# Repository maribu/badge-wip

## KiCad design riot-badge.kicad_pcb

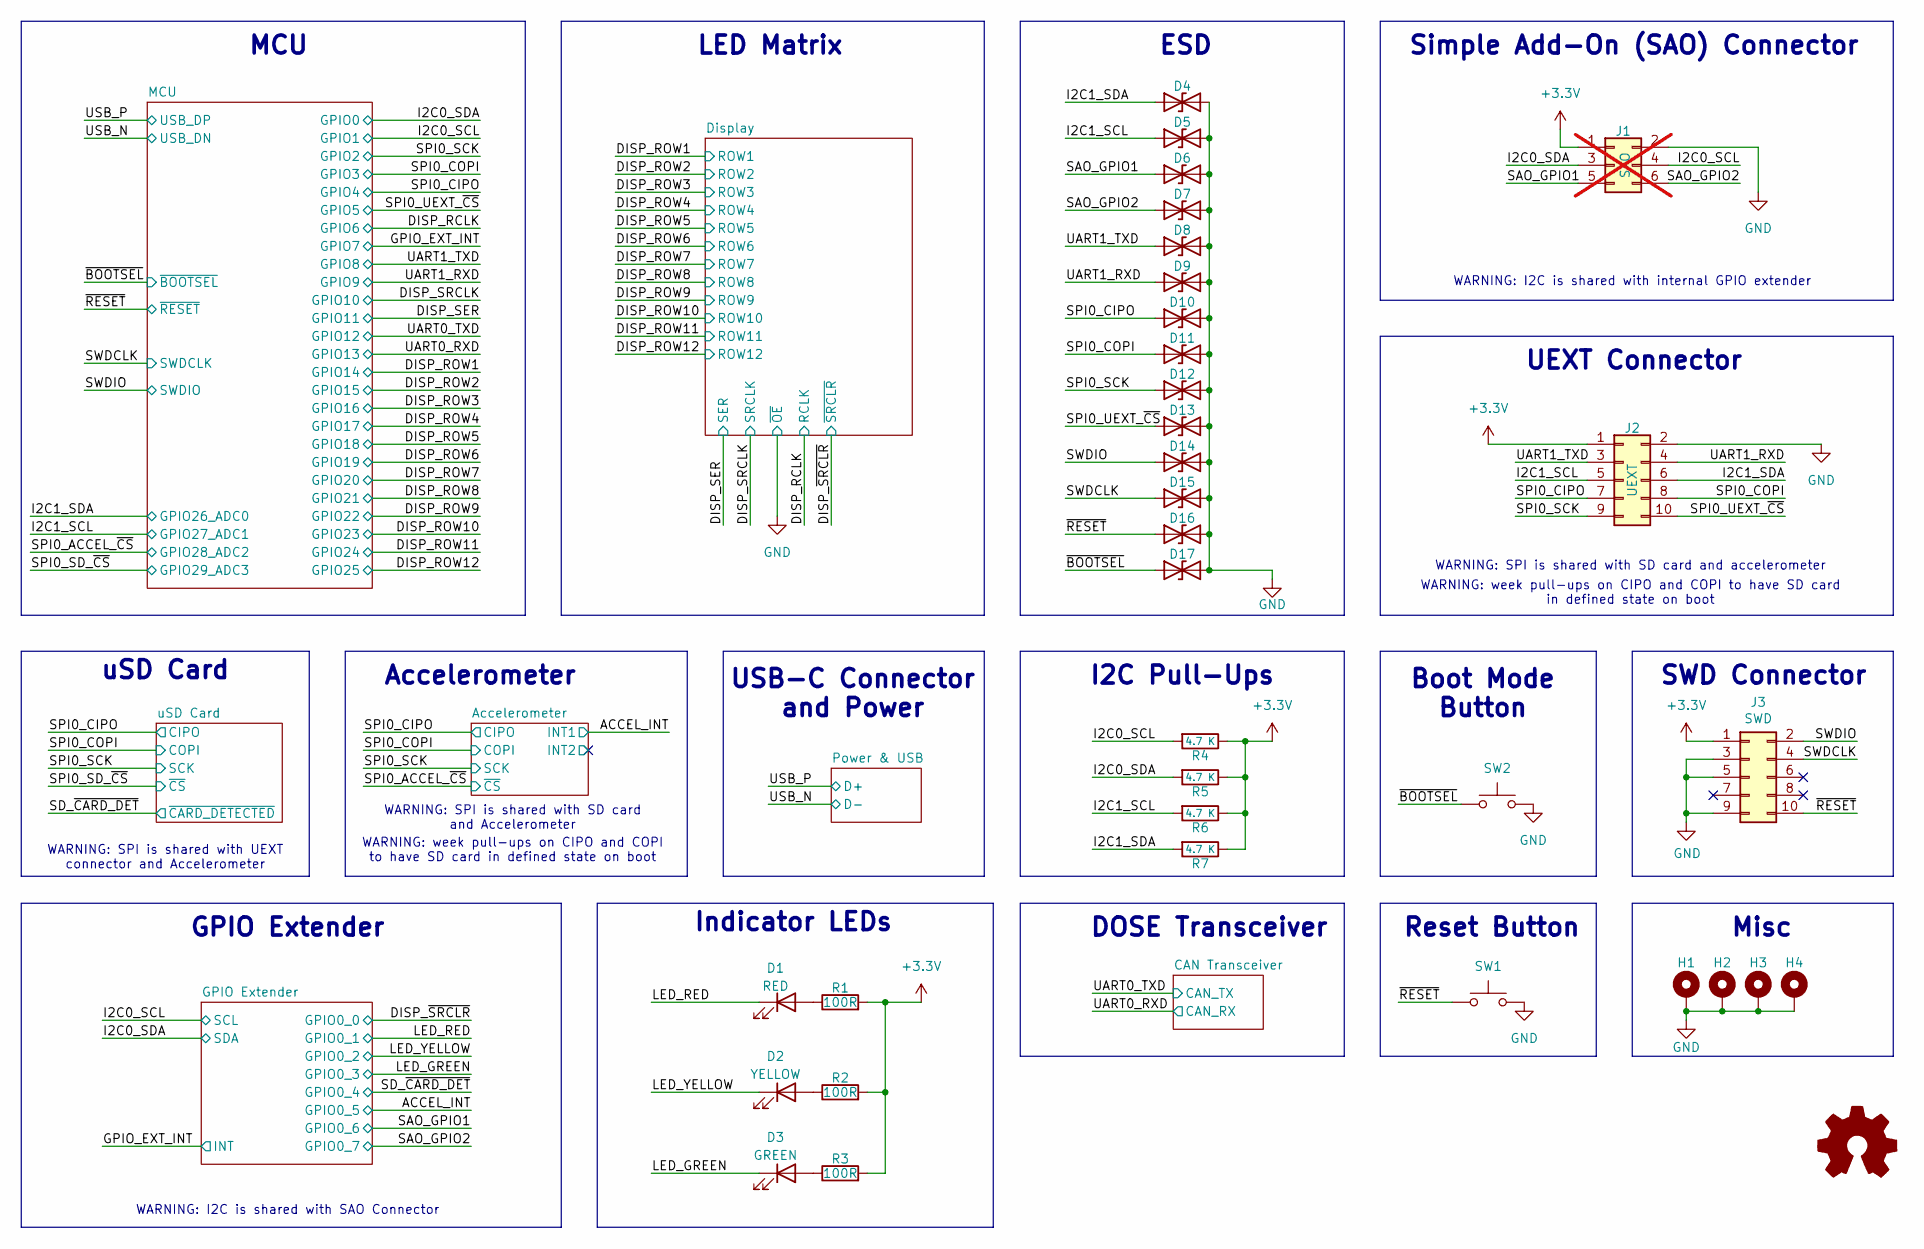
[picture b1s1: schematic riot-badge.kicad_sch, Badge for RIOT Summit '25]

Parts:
D1: RED; LED_0603_1608Metric; LCSC C2286
D2: YELLOW; LED_0805_2012Metric; LCSC C2296
D3: GREEN; LED_0805_2012Metric; LCSC C2297
D4, D5, D6, D7, D8, D9, D10, D11, D12, D13, D14, D15, D16, D17: D_TVS; SOD-882_L1.0-W0.6-BI; LCSC C7420372
G1: Logo_Open_Hardware_Small; OSHW-Logo2_7.3x6mm_SilkScreen
H1, H2, H3, H4: MountingHole_Pad; MountingHole_2.2mm_M2_DIN965_Pad
J1: SAO; PinSocket_2x03_P2.54mm_Vertical_SAO; LCSC C18164972; not fitted
J2: UEXT; HDR-TH_10P-P2.54-V-F-R2-C5-S2.54_GREENCONN; LCSC C7434489
J3: SWD; CONN-SMD_FTSH-105-01-L-DV-K-TR; LCSC C448647
R1, R2, R3: 100R; R_0402_1005Metric; LCSC C25076
R4, R5, R6, R7: 4.7 K; R_0402_1005Metric; LCSC C25900
SW1, SW2: SW_Push; SW-SMD_4P-L5.1-W5.1-P3.70-LS6.5-TL_H1.5; LCSC C318884

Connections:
+3.3V: J1.1, J2.1, J3.1, R1.2, R2.2, R3.2, R4.1, R5.1, R6.1, R7.1; also elsewhere on the board
/I2C0_SCL: J1.4, R4.2; also elsewhere on the board
/I2C0_SDA: J1.3, R5.2; also elsewhere on the board
/I2C1_SCL: D5.1 (A1), J2.5, R6.2; also elsewhere on the board
/I2C1_SDA: D4.1 (A1), J2.6, R7.2; also elsewhere on the board
/LED_GREEN: D3.1 (K); also elsewhere on the board
/LED_RED: D1.1 (K); also elsewhere on the board
/LED_YELLOW: D2.1 (K); also elsewhere on the board
/SAO_GPIO1: D6.1 (A1), J1.5; also elsewhere on the board
/SAO_GPIO2: D7.1 (A1), J1.6; also elsewhere on the board
/SPI0_CIPO: D10.1 (A1), J2.7; also elsewhere on the board
/SPI0_COPI: D11.1 (A1), J2.8; also elsewhere on the board
/SPI0_SCK: D12.1 (A1), J2.9; also elsewhere on the board
/SPI0_UEXT_~CS: D13.1 (A1), J2.10; also elsewhere on the board
/SWDCLK: D15.1 (A1), J3.4; also elsewhere on the board
/SWDIO: D14.1 (A1), J3.2; also elsewhere on the board
/UART1_RXD: D9.1 (A1), J2.4; also elsewhere on the board
/UART1_TXD: D8.1 (A1), J2.3; also elsewhere on the board
/~BOOTSEL: D17.1 (A1), SW2.1; also elsewhere on the board
/~RESET: D16.1 (A1), J3.10, SW1.1; also elsewhere on the board
GND: D4.2 (A2), D5.2 (A2), D6.2 (A2), D7.2 (A2), D8.2 (A2), D9.2 (A2), D10.2 (A2), D11.2 (A2), D12.2 (A2), D13.2 (A2), D14.2 (A2), D15.2 (A2), D16.2 (A2), D17.2 (A2), H1.1, H2.1, H3.1, H4.1, J1.2, J2.2, J3.3, J3.5, J3.9, SW1.2, SW2.2; also elsewhere on the board
unnamed: D1.2 (A), R1.1
unnamed: D2.2 (A), R2.1
unnamed: D3.2 (A), R3.1

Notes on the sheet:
UEXT Connector
Misc
uSD Card
GPIO Extender
Boot Mode Button
Indicator LEDs
WARNING: week pull-ups on CIPO and COPI to have SD card in defined state on boot
Reset Button
LED Matrix
WARNING: SPI is shared with UEXT connector and Accelerometer
DOSE Transceiver
ESD
WARNING: SPI is shared with SD card and accelerometer
I2C Pull-Ups
WARNING: I2C is shared with internal GPIO extender
WARNING: I2C is shared with SAO Connector
Simple Add-On (SAO) Connector
SWD Connector
WARNING: week pull-ups on CIPO and COPI to have SD card in defined state on boot
USB-C Connector and Power
WARNING: SPI is shared with SD card and Accelerometer
MCU
Accelerometer

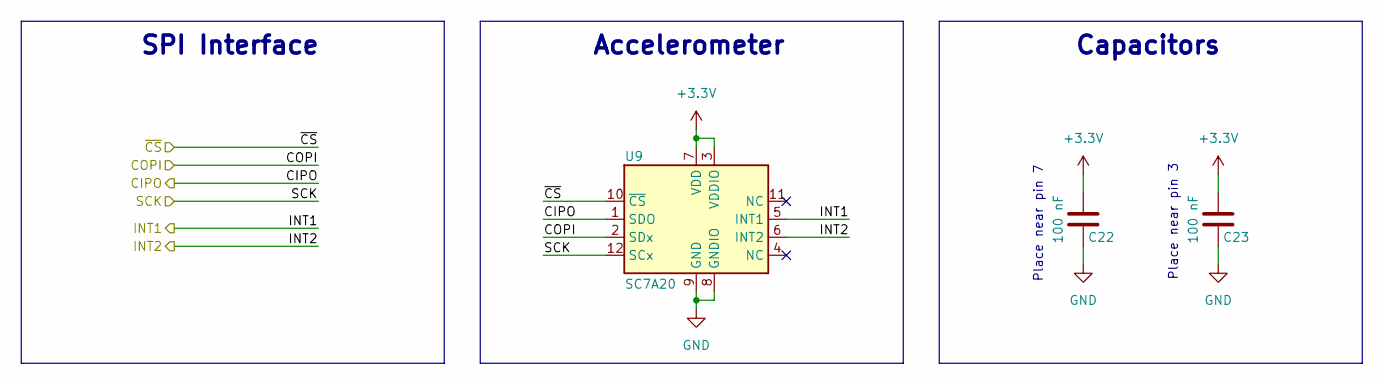
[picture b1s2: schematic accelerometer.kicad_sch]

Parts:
C22, C23: 100 nF; C_0402_1005Metric; LCSC C1525
U9: SC7A20; LGA-12_2x2mm_P0.5mm

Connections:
+3.3V: C22.1, C23.1, U9.3 (VDDIO), U9.7 (VDD); also elsewhere on the board
/ACCEL_INT: U9.5 (INT1); also elsewhere on the board
/Accelerometer/INT2: U9.6 (INT2)
/SPI0_ACCEL_~CS: U9.10 (~CS); also elsewhere on the board
/SPI0_CIPO: U9.1 (SDO); also elsewhere on the board
/SPI0_COPI: U9.2 (SDx); also elsewhere on the board
/SPI0_SCK: U9.12 (SCx); also elsewhere on the board
GND: C22.2, C23.2, U9.8 (GNDIO), U9.9 (GND); also elsewhere on the board

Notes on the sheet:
SPI Interface
Capacitors
Place near pin 7
Place near pin 3
Accelerometer

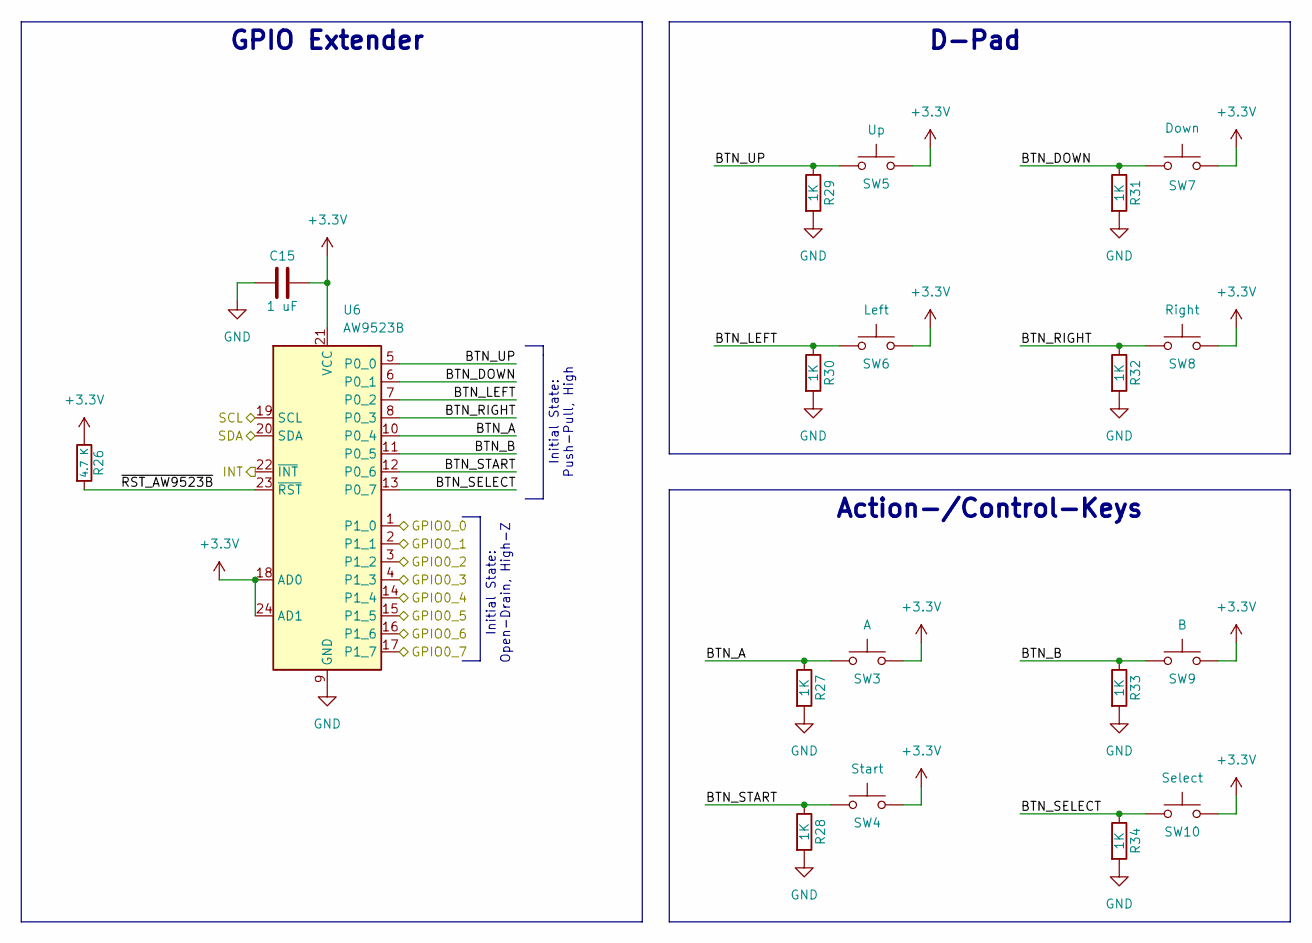
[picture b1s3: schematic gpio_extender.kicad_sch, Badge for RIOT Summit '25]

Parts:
C15: 1 uF; C_0402_1005Metric; LCSC C52923
R26: 4.7 K; R_0402_1005Metric; LCSC C25900
R27, R28, R29, R30, R31, R32, R33, R34: 1K; R_0402_1005Metric; LCSC C11702
SW3, SW4, SW5, SW6, SW7, SW8, SW9, SW10: SW_Push; SW-SMD_4P-L5.1-W5.1-P3.70-LS6.5-TL_H1.5; LCSC C318884
U6: AW9523B; QFN-24-1EP_4x4mm_P0.5mm_EP2.7x2.7mm

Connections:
+3.3V: C15.2, R26.1, SW3.2, SW4.2, SW5.2, SW6.2, SW7.2, SW8.2, SW9.2, SW10.2, U6.18 (AD0), U6.21 (VCC), U6.24 (AD1); also elsewhere on the board
/ACCEL_INT: U6.15 (P1_5); also elsewhere on the board
/DISP_~SRCLR: U6.1 (P1_0); also elsewhere on the board
/GPIO Extender/BTN_A: R27.1, SW3.1, U6.10 (P0_4)
/GPIO Extender/BTN_B: R33.1, SW9.1, U6.11 (P0_5)
/GPIO Extender/BTN_DOWN: R31.1, SW7.1, U6.6 (P0_1)
/GPIO Extender/BTN_LEFT: R30.1, SW6.1, U6.7 (P0_2)
/GPIO Extender/BTN_RIGHT: R32.1, SW8.1, U6.8 (P0_3)
/GPIO Extender/BTN_SELECT: R34.1, SW10.1, U6.13 (P0_7)
/GPIO Extender/BTN_START: R28.1, SW4.1, U6.12 (P0_6)
/GPIO Extender/BTN_UP: R29.1, SW5.1, U6.5 (P0_0)
/GPIO Extender/~RST_AW9523B: R26.2, U6.23 (~RST)
/GPIO_EXT_INT: U6.22 (~INT); also elsewhere on the board
/I2C0_SCL: U6.19 (SCL); also elsewhere on the board
/I2C0_SDA: U6.20 (SDA); also elsewhere on the board
/LED_GREEN: U6.4 (P1_3); also elsewhere on the board
/LED_RED: U6.2 (P1_1); also elsewhere on the board
/LED_YELLOW: U6.3 (P1_2); also elsewhere on the board
/SAO_GPIO1: U6.16 (P1_6); also elsewhere on the board
/SAO_GPIO2: U6.17 (P1_7); also elsewhere on the board
/SD_~CARD_DET: U6.14 (P1_4); also elsewhere on the board
GND: C15.1, R27.2, R28.2, R29.2, R30.2, R31.2, R32.2, R33.2, R34.2, U6.9 (GND), U6.25 (GND); also elsewhere on the board

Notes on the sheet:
Initial State: Push-Pull, High
D-Pad
Action-/Control-Keys
GPIO Extender
Initial State: Open-Drain, High-Z

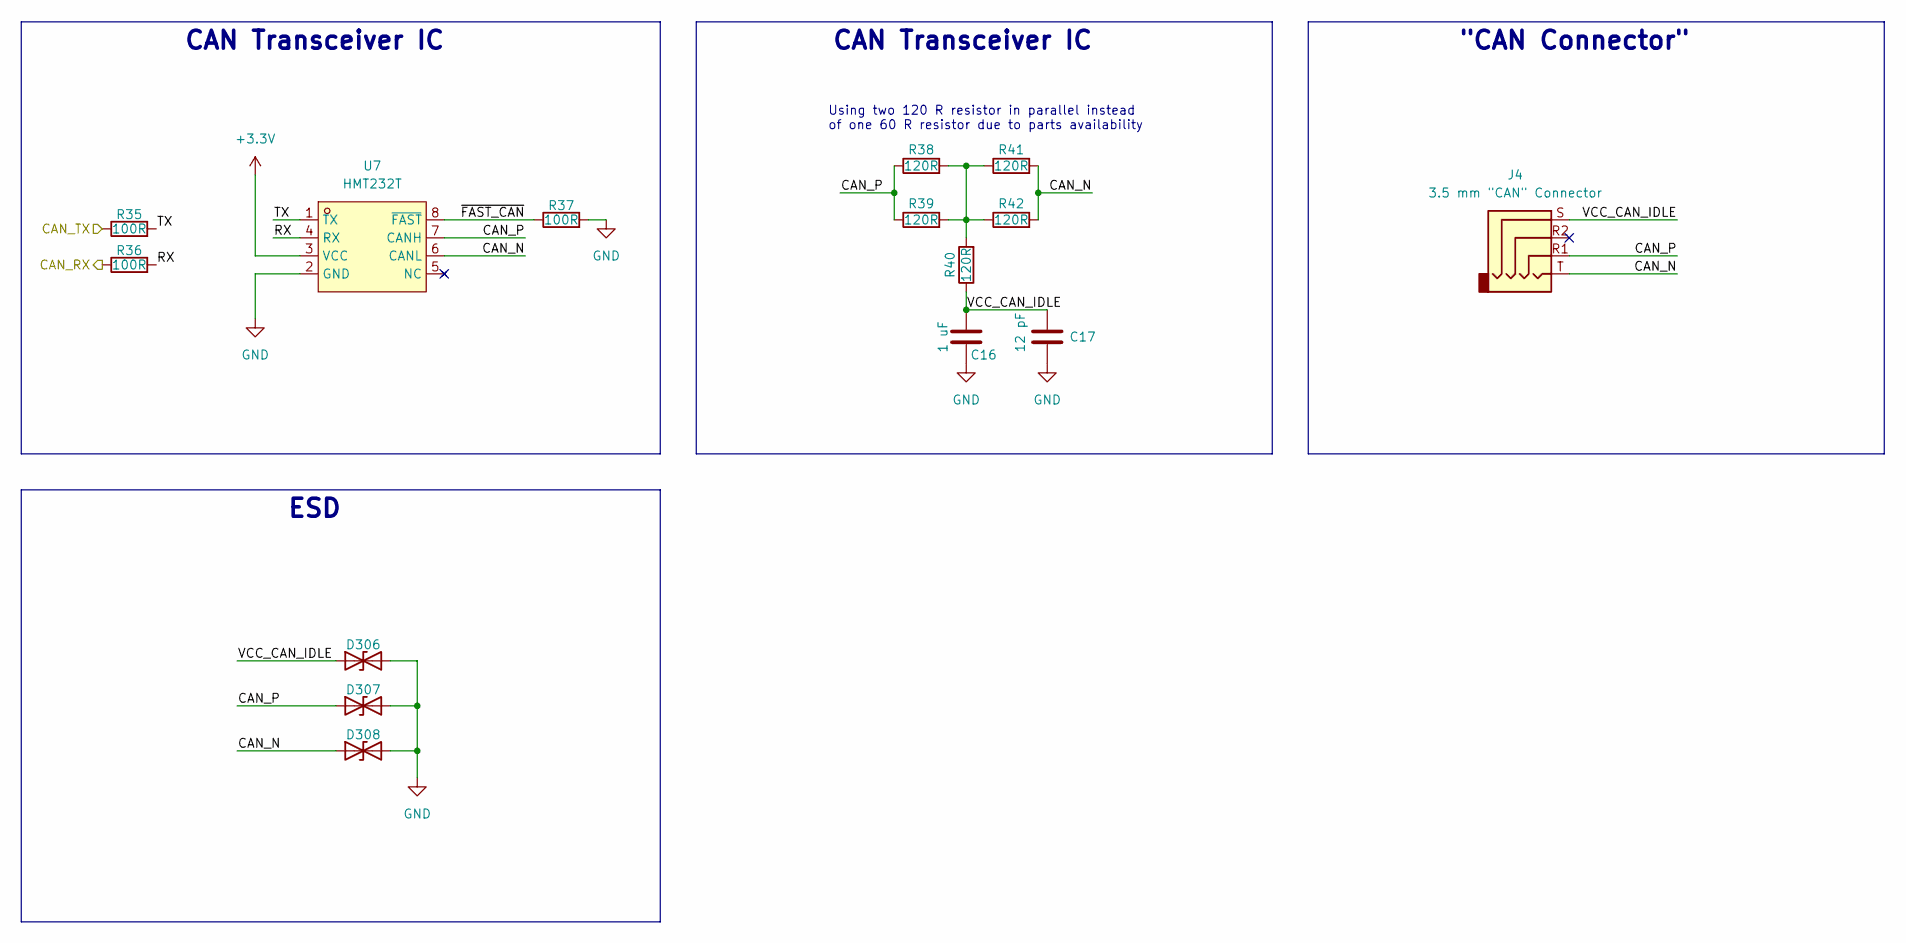
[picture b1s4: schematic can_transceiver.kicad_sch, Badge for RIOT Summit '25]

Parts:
C16: 1 uF; C_0402_1005Metric; LCSC C52923
C17: 12 pF; C_0402_1005Metric; LCSC C1547
D306, D307, D308: D_TVS; SOD-882_L1.0-W0.6-BI; LCSC C7420372
J4: 3.5 mm "CAN" Connector; Jack_3.5mm_PJ-320D; LCSC C22459515
R35, R36, R37: 100R; R_0402_1005Metric; LCSC C25076
R38, R39, R40, R41, R42: 120R; R_0402_1005Metric; LCSC C25079
U7: HMT232T; SOIC-8_3.9x4.9mm_P1.27mm; LCSC C45662327

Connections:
+3.3V: U7.3 (VCC); also elsewhere on the board
/CAN Transceiver/CAN_N: D308.1 (A1), J4.T, R41.2, R42.2, U7.6 (CANL)
/CAN Transceiver/CAN_P: D307.1 (A1), J4.R1, R38.1, R39.1, U7.7 (CANH)
/CAN Transceiver/RX: R36.2, U7.4 (RX)
/CAN Transceiver/TX: R35.2, U7.1 (TX)
/CAN Transceiver/VCC_CAN_IDLE: C16.1, C17.1, D306.1 (A1), J4.S, R40.1
/CAN Transceiver/~FAST_CAN: R37.1, U7.8 (~FAST)
/UART0_RXD: R36.1; also elsewhere on the board
/UART0_TXD: R35.1; also elsewhere on the board
GND: C16.2, C17.2, D306.2 (A2), D307.2 (A2), D308.2 (A2), R37.2, U7.2 (GND); also elsewhere on the board
unnamed: R38.2, R39.2, R40.2, R41.1, R42.1

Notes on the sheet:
"CAN Connector"
CAN Transceiver IC
ESD
Using two 120 R resistor in parallel instead of one 60 R resistor due to parts availability

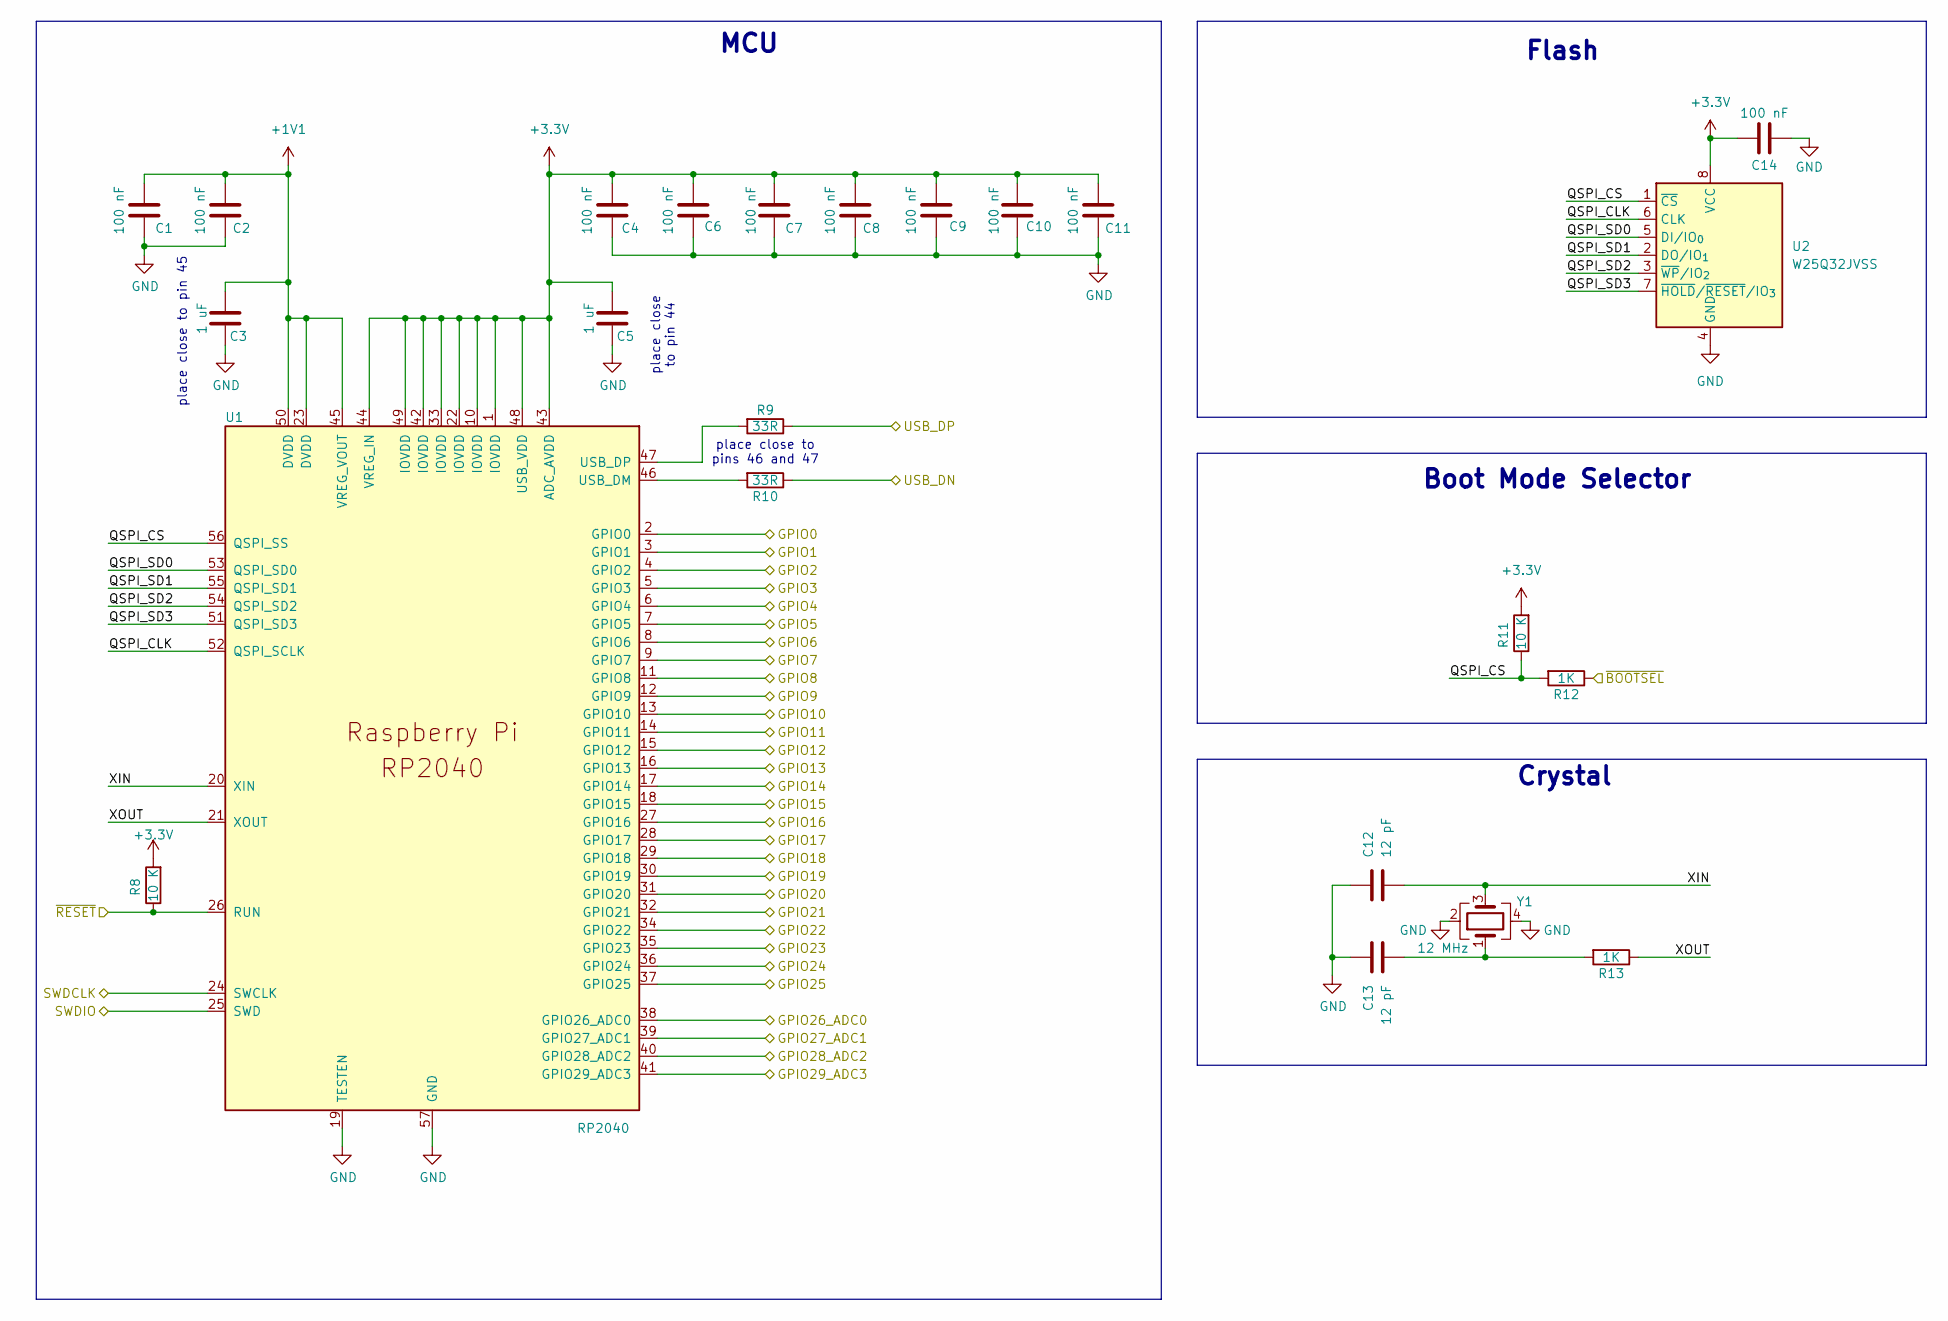
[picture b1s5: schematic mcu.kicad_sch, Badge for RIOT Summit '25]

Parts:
C1, C2, C4, C6, C7, C8, C9, C10, C11, C14: 100 nF; C_0402_1005Metric; LCSC C1525
C3, C5: 1 uF; C_0402_1005Metric; LCSC C52923
C12, C13: 12 pF; C_0402_1005Metric; LCSC C1547
R8, R11: 10 K; R_0402_1005Metric; LCSC C25744
R9, R10: 33R; R_0402_1005Metric; LCSC C25105
R12, R13: 1K; R_0402_1005Metric; LCSC C11702
U1: RP2040; RP2040-QFN-56; LCSC C2040
U2: W25Q32JVSS; SOIC-8_5.3x5.3mm_P1.27mm
Y1: 12 MHz; Crystal_SMD_3225-4Pin_3.2x2.5mm; LCSC C9002

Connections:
+1V1: C1.1, C2.2, C3.1, U1.23 (DVDD), U1.45 (VREG_VOUT), U1.50 (DVDD)
+3.3V: C4.1, C5.1, C6.1, C7.1, C8.2, C9.1, C10.1, C11.1, C14.1, R8.2, R11.2, U1.1 (IOVDD), U1.10 (IOVDD), U1.22 (IOVDD), U1.33 (IOVDD), U1.42 (IOVDD), U1.43 (ADC_AVDD), U1.44 (VREG_IN), U1.48 (USB_VDD), U1.49 (IOVDD), U2.8 (VCC); also elsewhere on the board
/DISP_RCLK: U1.8 (GPIO6); also elsewhere on the board
/DISP_ROW1: U1.17 (GPIO14); also elsewhere on the board
/DISP_ROW2: U1.18 (GPIO15); also elsewhere on the board
/DISP_ROW3: U1.27 (GPIO16); also elsewhere on the board
/DISP_ROW4: U1.28 (GPIO17); also elsewhere on the board
/DISP_ROW5: U1.29 (GPIO18); also elsewhere on the board
/DISP_ROW6: U1.30 (GPIO19); also elsewhere on the board
/DISP_ROW7: U1.31 (GPIO20); also elsewhere on the board
/DISP_ROW8: U1.32 (GPIO21); also elsewhere on the board
/DISP_ROW9: U1.34 (GPIO22); also elsewhere on the board
/DISP_ROW10: U1.35 (GPIO23); also elsewhere on the board
/DISP_ROW11: U1.36 (GPIO24); also elsewhere on the board
/DISP_ROW12: U1.37 (GPIO25); also elsewhere on the board
/DISP_SER: U1.14 (GPIO11); also elsewhere on the board
/DISP_SRCLK: U1.13 (GPIO10); also elsewhere on the board
/GPIO_EXT_INT: U1.9 (GPIO7); also elsewhere on the board
/I2C0_SCL: U1.3 (GPIO1); also elsewhere on the board
/I2C0_SDA: U1.2 (GPIO0); also elsewhere on the board
/I2C1_SCL: U1.39 (GPIO27_ADC1); also elsewhere on the board
/I2C1_SDA: U1.38 (GPIO26_ADC0); also elsewhere on the board
/MCU/QSPI_CLK: U1.52 (QSPI_SCLK), U2.6 (CLK)
/MCU/QSPI_CS: R11.1, R12.2, U1.56 (QSPI_SS), U2.1 (~CS)
/MCU/QSPI_SD0: U1.53 (QSPI_SD0), U2.5 (DI/IO_{0})
/MCU/QSPI_SD1: U1.55 (QSPI_SD1), U2.2 (DO/IO_{1})
/MCU/QSPI_SD2: U1.54 (QSPI_SD2), U2.3 (~WP/IO_{2})
/MCU/QSPI_SD3: U1.51 (QSPI_SD3), U2.7 (~HOLD/~RESET/IO_{3})
/MCU/XIN: C12.2, U1.20 (XIN), Y1.3
/MCU/XOUT: R13.1, U1.21 (XOUT)
/SPI0_ACCEL_~CS: U1.40 (GPIO28_ADC2); also elsewhere on the board
/SPI0_CIPO: U1.6 (GPIO4); also elsewhere on the board
/SPI0_COPI: U1.5 (GPIO3); also elsewhere on the board
/SPI0_SCK: U1.4 (GPIO2); also elsewhere on the board
/SPI0_SD_~CS: U1.41 (GPIO29_ADC3); also elsewhere on the board
/SPI0_UEXT_~CS: U1.7 (GPIO5); also elsewhere on the board
/SWDCLK: U1.24 (SWCLK); also elsewhere on the board
/SWDIO: U1.25 (SWD); also elsewhere on the board
/UART0_RXD: U1.16 (GPIO13); also elsewhere on the board
/UART0_TXD: U1.15 (GPIO12); also elsewhere on the board
/UART1_RXD: U1.12 (GPIO9); also elsewhere on the board
/UART1_TXD: U1.11 (GPIO8); also elsewhere on the board
/USB_N: R10.1; also elsewhere on the board
/USB_P: R9.1; also elsewhere on the board
/~BOOTSEL: R12.1; also elsewhere on the board
/~RESET: R8.1, U1.26 (RUN); also elsewhere on the board
GND: C1.2, C2.1, C3.2, C4.2, C5.2, C6.2, C7.2, C8.1, C9.2, C10.2, C11.2, C12.1, C13.1, C14.2, U1.19 (TESTEN), U1.57 (GND), U2.4 (GND), Y1.2, Y1.4; also elsewhere on the board
unnamed: C13.2, R13.2, Y1.1
unnamed: R10.2, U1.46 (USB_DM)
unnamed: R9.2, U1.47 (USB_DP)

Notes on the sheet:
Crystal
Flash
Boot Mode Selector
place close to pins 46 and 47
place close to pin 44
place close to pin 45
MCU

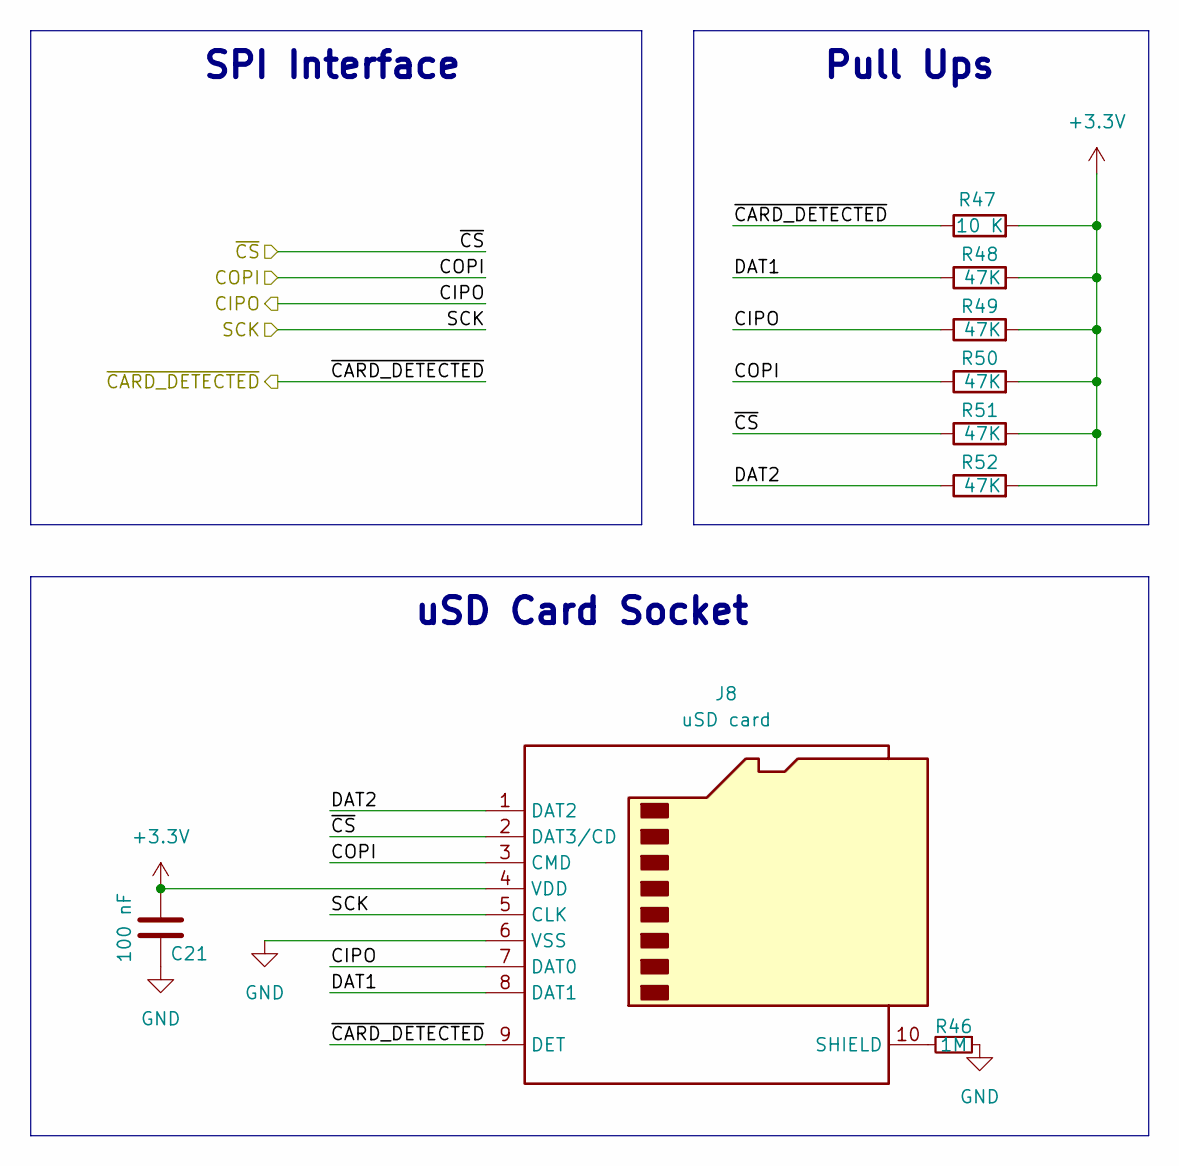
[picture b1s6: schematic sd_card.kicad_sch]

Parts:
C21: 100 nF; C_0402_1005Metric; LCSC C1525
J8: uSD card; uSD_CARD; LCSC C5454948
R46: 1M; R_0402_1005Metric; LCSC C26083
R47: 10 K; R_0402_1005Metric; LCSC C25744
R48, R49, R50, R51, R52: 47K; R_0402_1005Metric; LCSC C25792

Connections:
+3.3V: C21.1, J8.4 (VDD), R47.2, R48.2, R49.2, R50.2, R51.2, R52.2; also elsewhere on the board
/SD_~CARD_DET: J8.9 (DET), R47.1; also elsewhere on the board
/SPI0_CIPO: J8.7 (DAT0), R49.1; also elsewhere on the board
/SPI0_COPI: J8.3 (CMD), R50.1; also elsewhere on the board
/SPI0_SCK: J8.5 (CLK); also elsewhere on the board
/SPI0_SD_~CS: J8.2 (DAT3/CD), R51.1; also elsewhere on the board
/uSD Card/DAT1: J8.8 (DAT1), R48.1
/uSD Card/DAT2: J8.1 (DAT2), R52.1
GND: C21.2, J8.6 (VSS), R46.1; also elsewhere on the board
unnamed: J8.10 (SHIELD), R46.2

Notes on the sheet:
Pull Ups
uSD Card Socket
SPI Interface

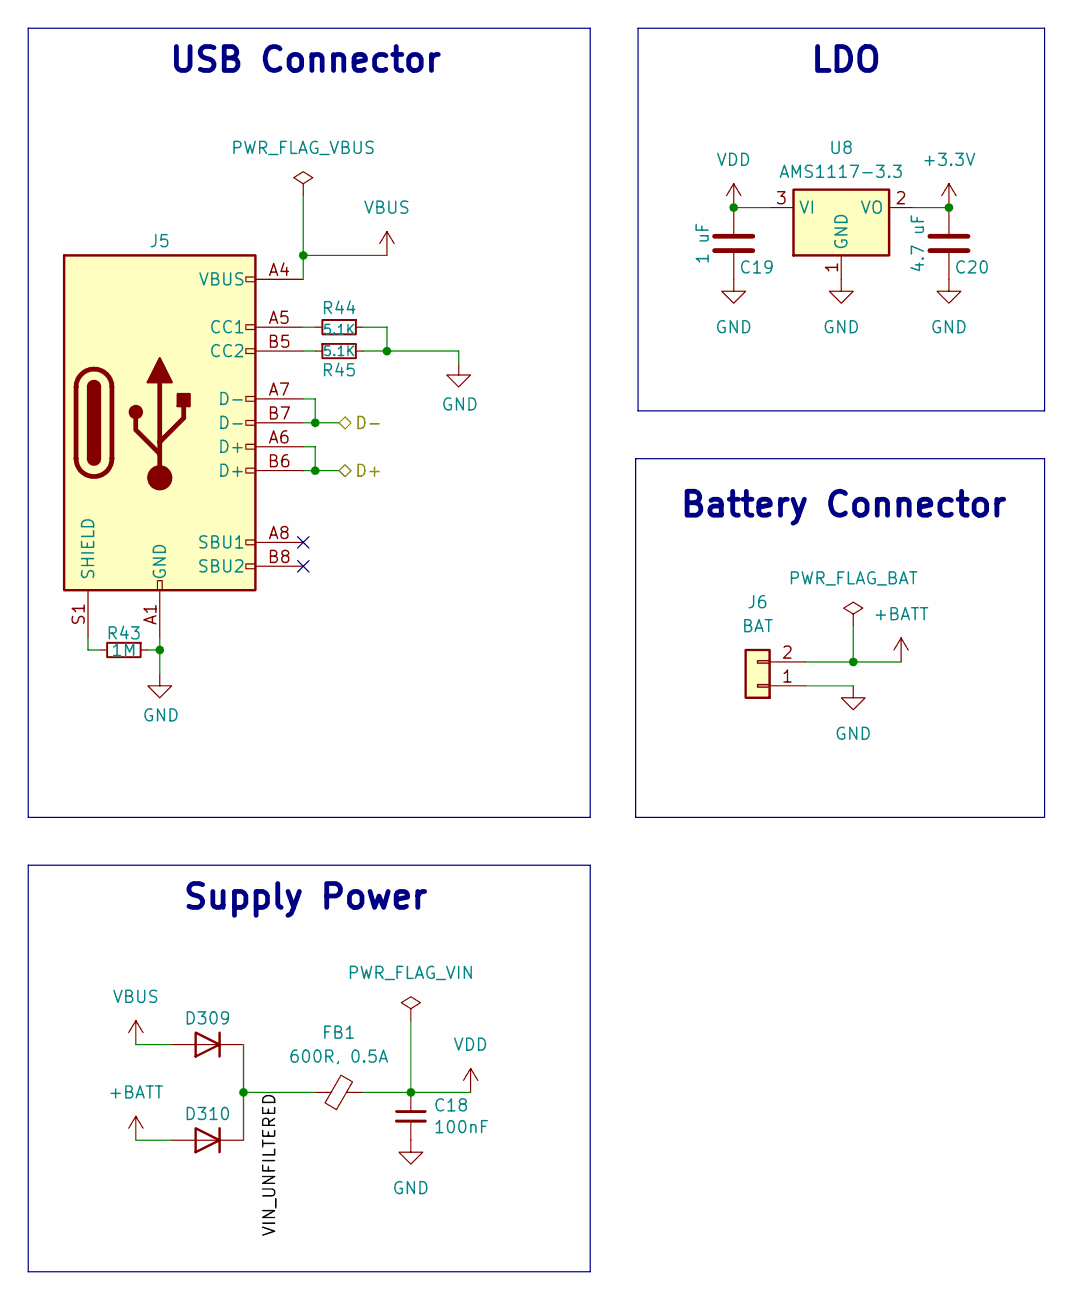
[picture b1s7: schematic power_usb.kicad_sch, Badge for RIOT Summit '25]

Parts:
C18: 100nF; C_0402_1005Metric; LCSC C1525
C19: 1 uF; C_0402_1005Metric; LCSC C52923
C20: 4.7 uF; C_0402_1005Metric; LCSC C23733
D309, D310: D; D_SOD-123; LCSC C64898
FB1: 600R, 0.5A; L_0805_2012Metric; LCSC C1017
J5: USB_C_Receptacle_USB2.0_16P; USB_C_Receptacle_GCT_USB4105-xx-A_16P_TopMnt_Horizontal; LCSC C165948
J6: BAT; CONN-TH_2P-P2.00_KINGHELM_KH-PH-2P-Z; LCSC C2898945
R43: 1M; R_0402_1005Metric; LCSC C26083
R44, R45: 5.1K; R_0402_1005Metric; LCSC C25905
U8: AMS1117-3.3; SOT-223-3_TabPin2; LCSC C6186

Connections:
+3.3V: C20.1, U8.2 (VO); also elsewhere on the board
+BATT: D310.2 (A), J6.2
/Power & USB/VIN_UNFILTERED: D309.1 (K), D310.1 (K), FB1.1
/USB_N: J5.A7 (D-), J5.B7 (D-); also elsewhere on the board
/USB_P: J5.A6 (D+), J5.B6 (D+); also elsewhere on the board
GND: C18.2, C19.2, C20.2, J5.A1 (GND), J5.A12 (GND), J5.B1 (GND), J5.B12 (GND), J6.1, R43.1, R44.1, R45.2, U8.1 (GND); also elsewhere on the board
unnamed: J5.A5 (CC1), R44.2
unnamed: J5.B5 (CC2), R45.1
unnamed: J5.S1 (SHIELD), R43.2
VBUS: D309.2 (A), J5.A4 (VBUS), J5.A9 (VBUS), J5.B4 (VBUS), J5.B9 (VBUS)
VDD: C18.1, C19.1, FB1.2, U8.3 (VI)

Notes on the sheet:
LDO
USB Connector
Battery Connector
Supply Power
